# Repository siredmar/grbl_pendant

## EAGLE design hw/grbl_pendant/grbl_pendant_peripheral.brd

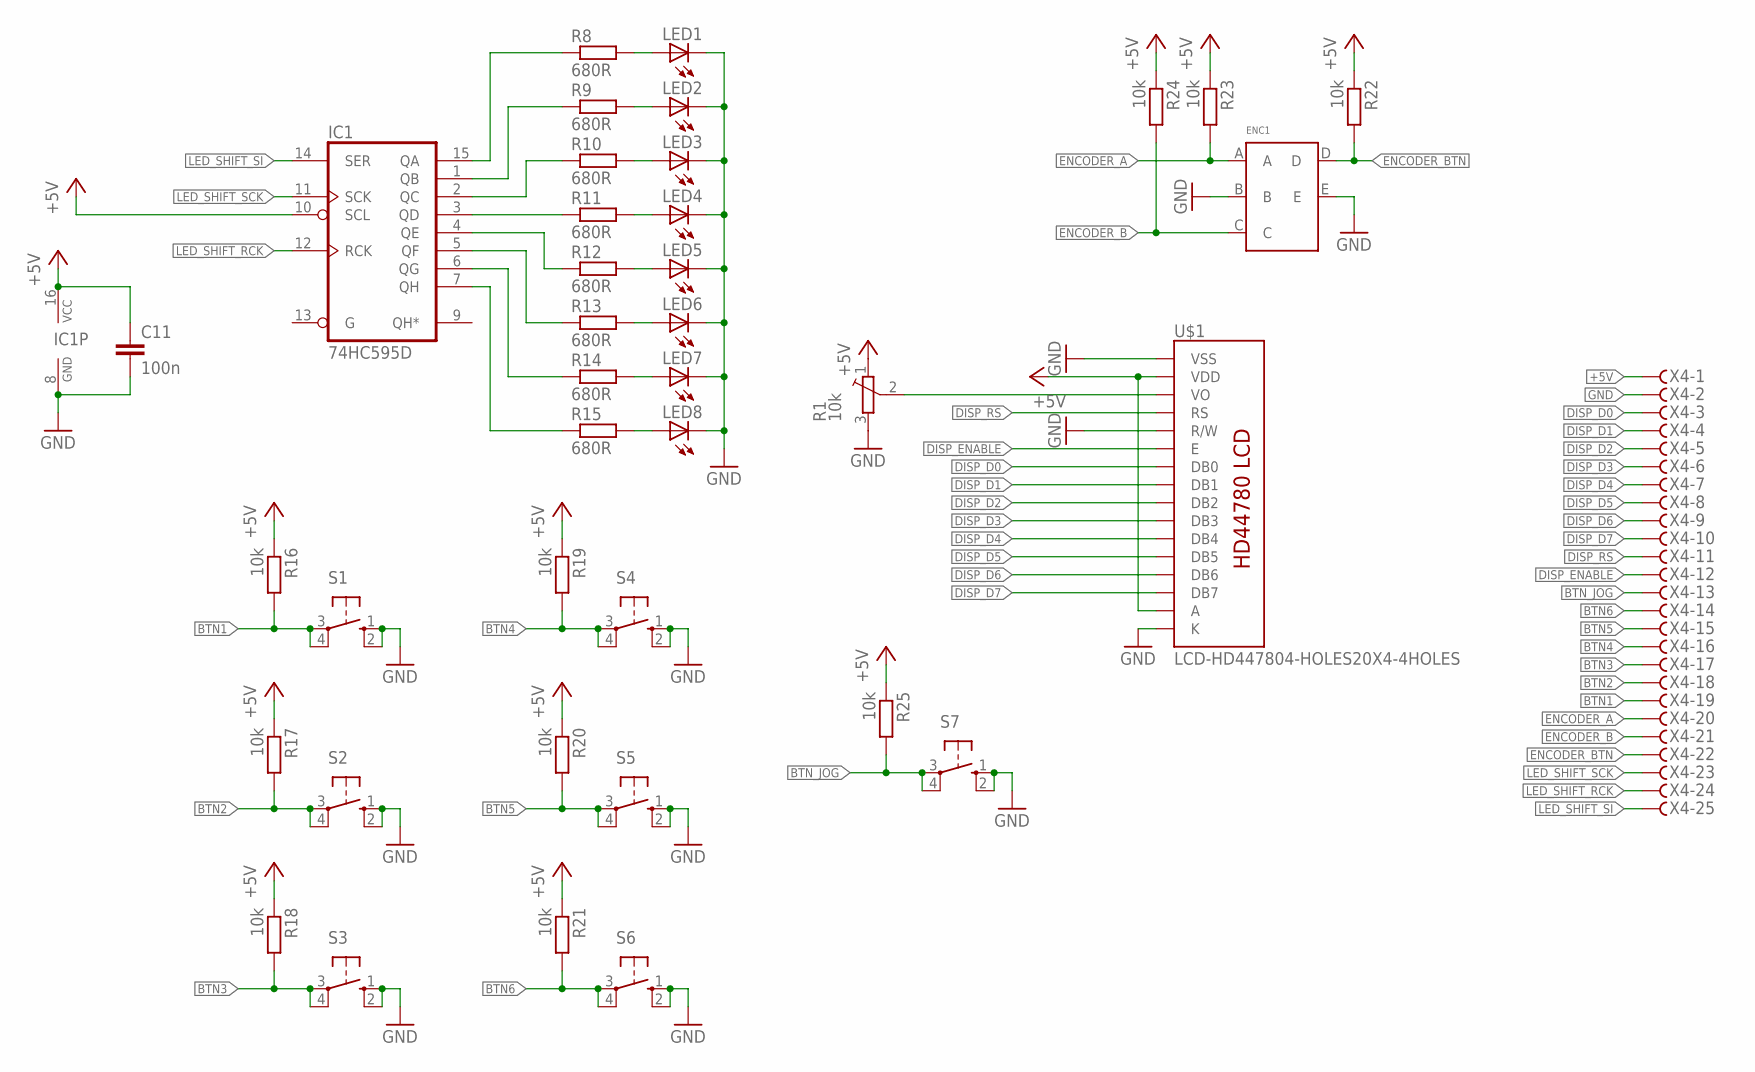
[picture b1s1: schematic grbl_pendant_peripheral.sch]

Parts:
C11: 100n; C0603K
ENC1: ENCODER
IC1: 74HC595D; SO16
LED1, LED2, LED3, LED4, LED5, LED6, LED7, LED8: LED5MM
R1: 10k; 35WR5KLFTR
R8, R9, R10, R11, R12, R13, R14, R15: 680R; R0603
R16, R17, R18, R19, R20, R21, R22, R23, R24, R25: 10k; R0603
S1, S2, S3, S4, S5, S6, S7: 10-XX; B3F-10XX
U$1: LCD-HD447804-HOLES20X4-4HOLES; LCD-20X4-4HOLES
X4: F25HPS; F25HP

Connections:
+5V: C11.1, IC1.10 (SCL), IC1.16 (VCC), R1.1 (E), R16.1, R17.1, R18.1, R19.1, R20.1, R21.1, R22.1, R23.1, R24.1, R25.1, U$1.P$2 (VDD), U$1.P$15 (A), X4.1
BTN1: R16.2, S1.3, S1.4 (P1), X4.19
BTN2: R17.2, S2.3, S2.4 (P1), X4.18
BTN3: R18.2, S3.3, S3.4 (P1), X4.17
BTN4: R19.2, S4.3, S4.4 (P1), X4.16
BTN5: R20.2, S5.3, S5.4 (P1), X4.15
BTN6: R21.2, S6.3, S6.4 (P1), X4.14
BTN_JOG: R25.2, S7.3, S7.4 (P1), X4.13
DISP_D0: U$1.P$7 (DB0), X4.3
DISP_D1: U$1.P$8 (DB1), X4.4
DISP_D2: U$1.P$9 (DB2), X4.5
DISP_D3: U$1.P$10 (DB3), X4.6
DISP_D4: U$1.P$11 (DB4), X4.7
DISP_D5: U$1.P$12 (DB5), X4.8
DISP_D6: U$1.P$13 (DB6), X4.9
DISP_D7: U$1.P$14 (DB7), X4.10
DISP_ENABLE: U$1.P$6 (E), X4.12
DISP_RS: U$1.P$4 (RS), X4.11
ENCODER_A: ENC1.A, R23.2, X4.20
ENCODER_B: ENC1.C, R24.2, X4.21
ENCODER_BTN: ENC1.D, R22.2, X4.22
GND: C11.2, ENC1.B, ENC1.E, IC1.8 (GND), LED1.K (C), LED2.K (C), LED3.K (C), LED4.K (C), LED5.K (C), LED6.K (C), LED7.K (C), LED8.K (C), R1.3 (A), S1.1 (S), S1.2 (S1), S2.1 (S), S2.2 (S1), S3.1 (S), S3.2 (S1), S4.1 (S), S4.2 (S1), S5.1 (S), S5.2 (S1), S6.1 (S), S6.2 (S1), S7.1 (S), S7.2 (S1), U$1.P$1 (VSS), U$1.P$5 (R/W), U$1.P$16 (K), X4.2
LED_SHIFT_RCK: IC1.12 (RCK), X4.24
LED_SHIFT_SCK: IC1.11 (SCK), X4.23
LED_SHIFT_SI: IC1.14 (SER), X4.25
unnamed: IC1.3 (QD), R11.1
unnamed: IC1.15 (QA), R8.1
unnamed: IC1.1 (QB), R9.1
unnamed: IC1.2 (QC), R10.1
unnamed: R1.2 (S), U$1.P$3 (VO)
unnamed: IC1.4 (QE), R12.1
unnamed: IC1.5 (QF), R13.1
unnamed: IC1.6 (QG), R14.1
unnamed: IC1.7 (QH), R15.1
unnamed: LED1.A, R8.2
unnamed: LED2.A, R9.2
unnamed: LED3.A, R10.2
unnamed: LED4.A, R11.2
unnamed: LED5.A, R12.2
unnamed: LED6.A, R13.2
unnamed: LED7.A, R14.2
unnamed: LED8.A, R15.2

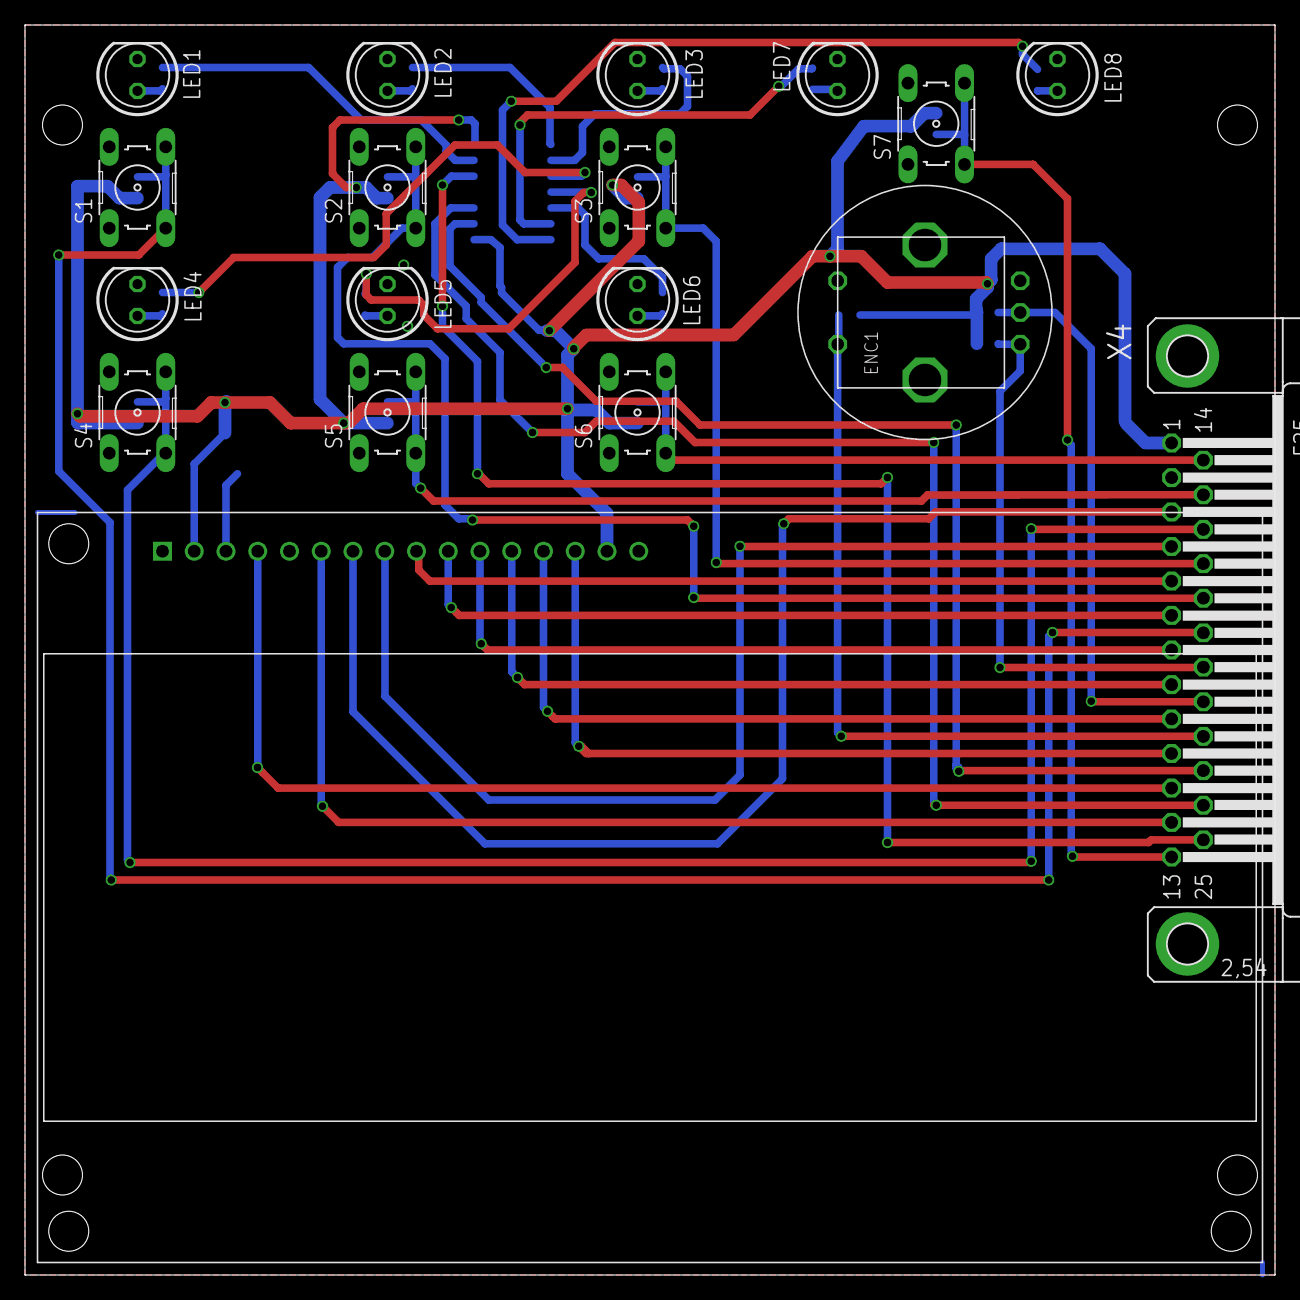
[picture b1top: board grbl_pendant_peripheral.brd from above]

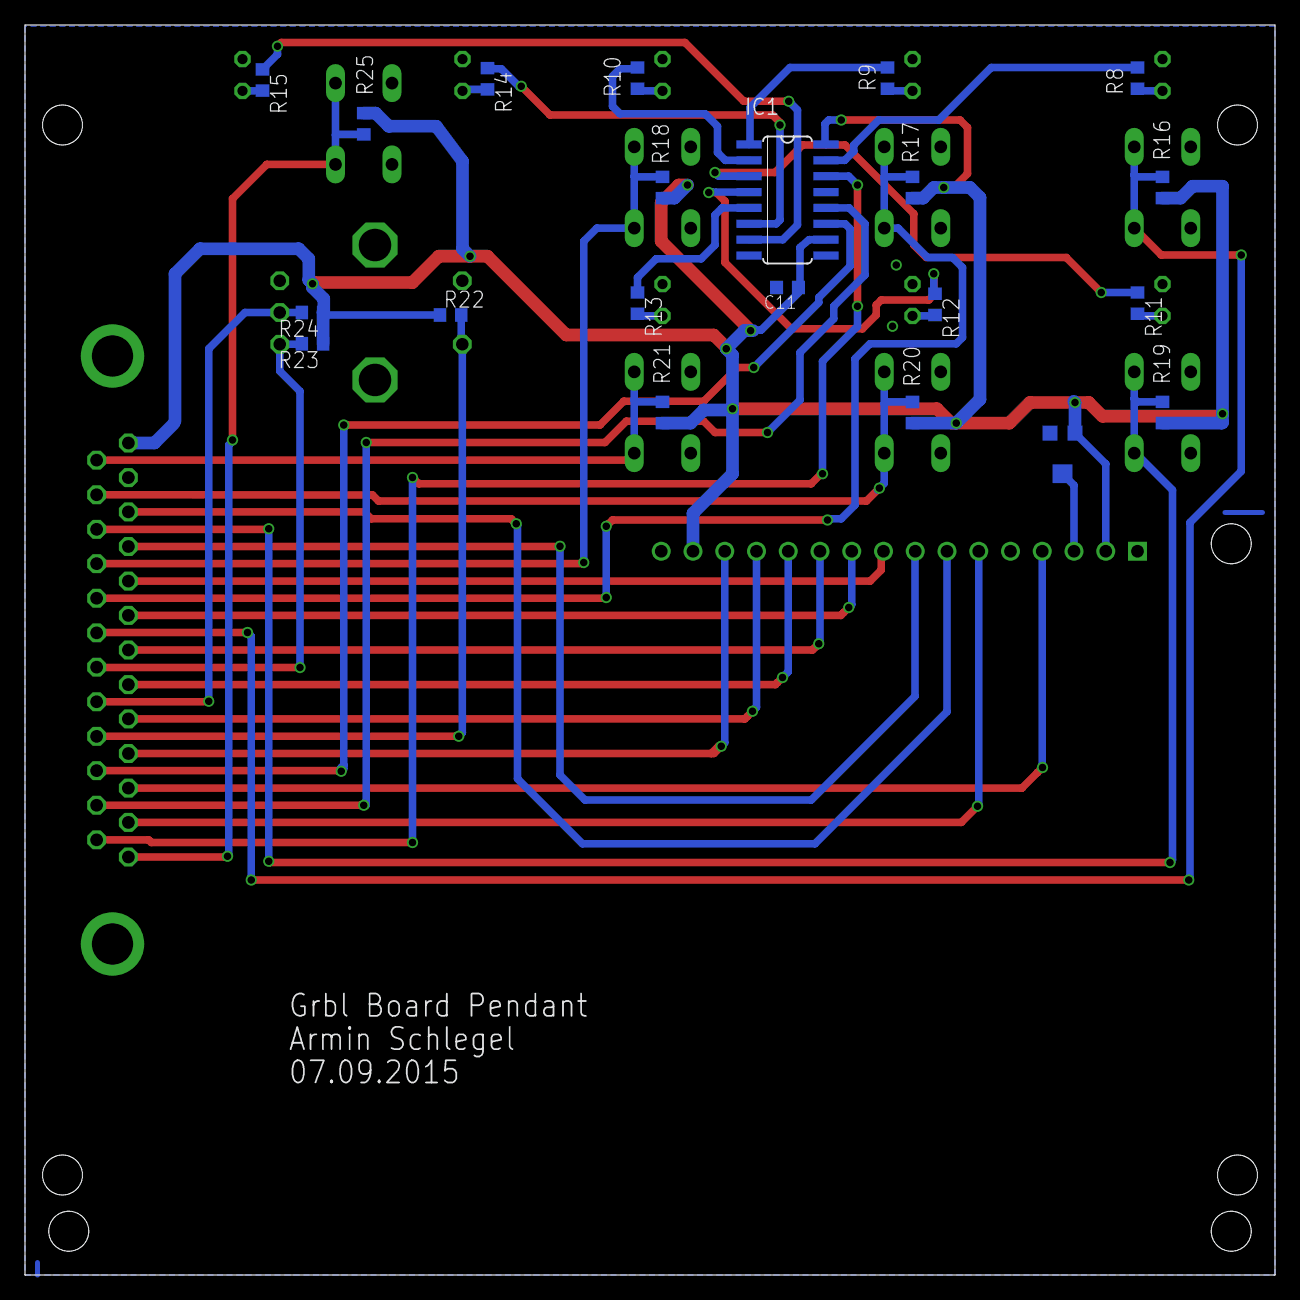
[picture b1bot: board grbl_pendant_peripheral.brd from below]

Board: 2 copper layers, 100.0 x 100.0 mm, 39 parts (21 on the bottom side), 42 nets.

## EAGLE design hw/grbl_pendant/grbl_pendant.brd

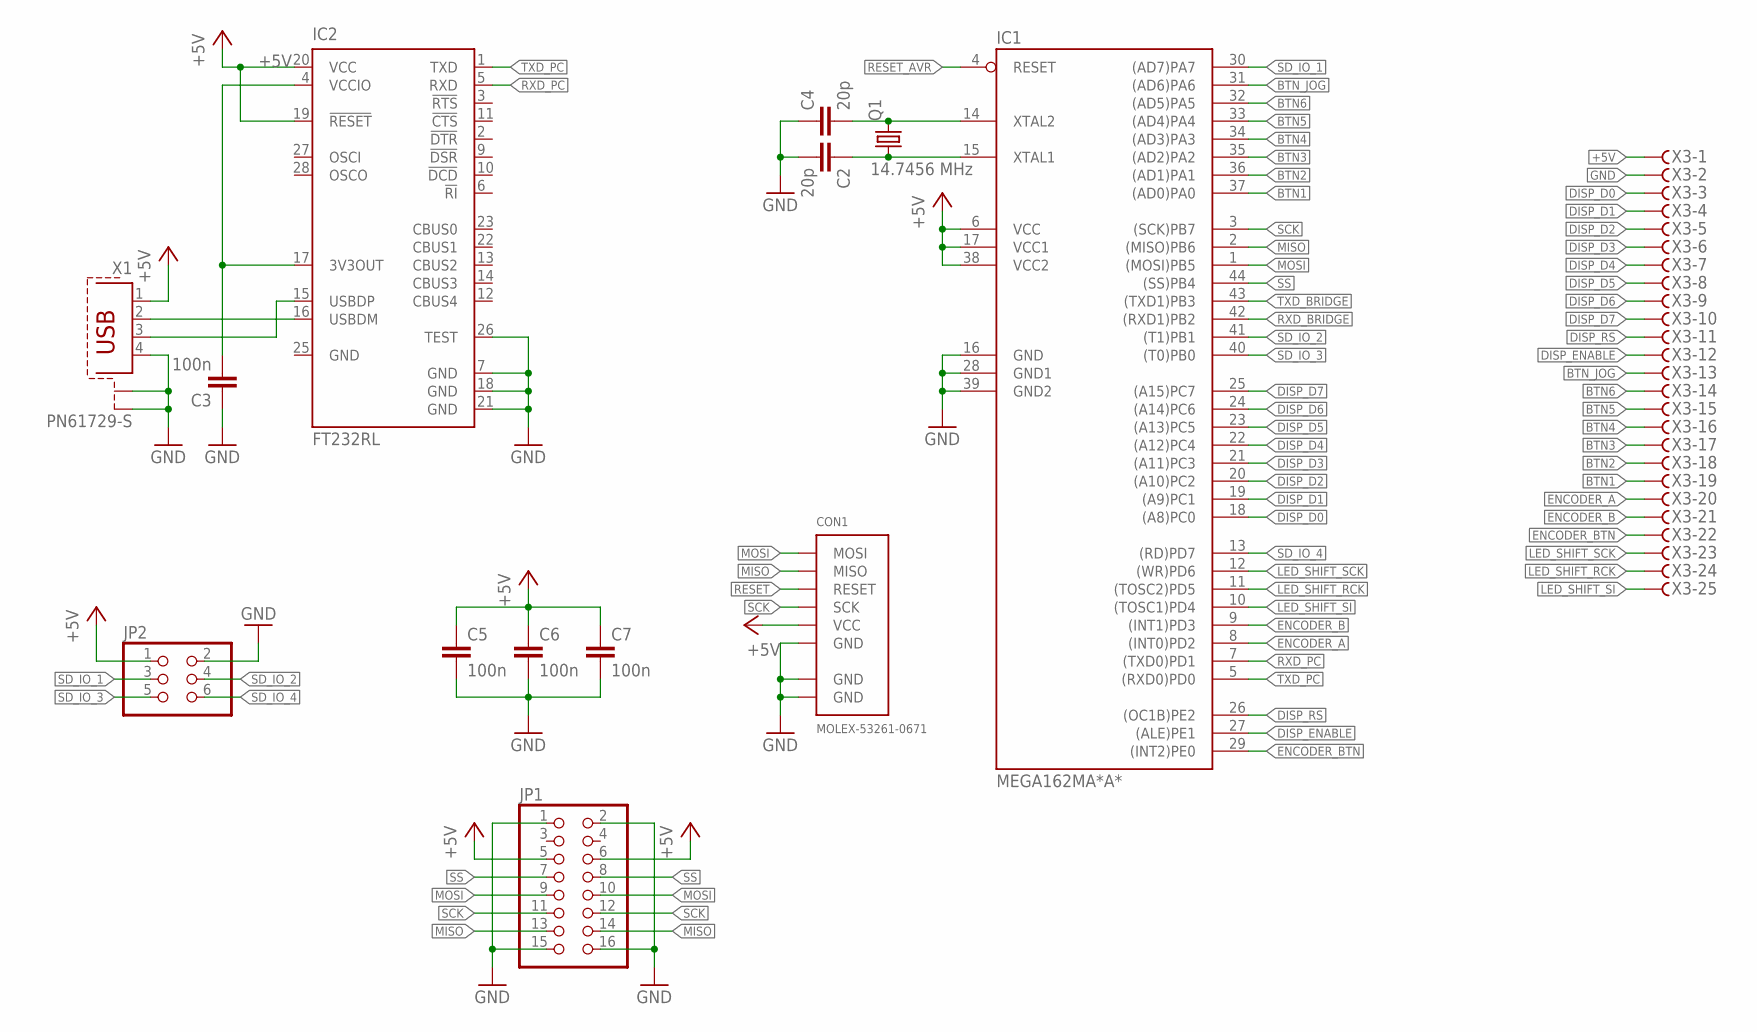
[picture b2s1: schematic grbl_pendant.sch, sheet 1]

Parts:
C2, C4: 20p; C0603K
C3: 100n; C0603
C5, C6, C7: 100n; C0603K
CON1: MOLEX-53261-0671
IC1: MEGA162MA*A*; TQFP44
IC2: FT232RL; SSOP28
JP1: PINHD-2X08_2.54; 2X08
JP2: PINHD-2X03_2.54; 2X03
Q1: 14.7456 MHz; HC49UP
X1: PN61729-S
X3: F25HPS; F25HP

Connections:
!RESET: CON1.3 (RESET)
+5V: C5.1, C6.1, C7.1, CON1.5 (VCC), IC1.6 (VCC), IC1.17 (VCC1), IC1.38 (VCC2), IC2.19 (!RESET), IC2.20 (VCC), JP1.5, JP1.6, JP2.1, X1.1, X3.1; also elsewhere on the board
BTN1: IC1.37 ((AD0)PA0), X3.19
BTN2: IC1.36 ((AD1)PA1), X3.18
BTN3: IC1.35 ((AD2)PA2), X3.17
BTN4: IC1.34 ((AD3)PA3), X3.16
BTN5: IC1.33 ((AD4)PA4), X3.15
BTN6: IC1.32 ((AD5)PA5), X3.14
BTN_JOG: IC1.31 ((AD6)PA6), X3.13
DISP_D0: IC1.18 ((A8)PC0), X3.3
DISP_D1: IC1.19 ((A9)PC1), X3.4
DISP_D2: IC1.20 ((A10)PC2), X3.5
DISP_D3: IC1.21 ((A11)PC3), X3.6
DISP_D4: IC1.22 ((A12)PC4), X3.7
DISP_D5: IC1.23 ((A13)PC5), X3.8
DISP_D6: IC1.24 ((A14)PC6), X3.9
DISP_D7: IC1.25 ((A15)PC7), X3.10
DISP_ENABLE: IC1.27 ((ALE)PE1), X3.12
DISP_RS: IC1.26 ((OC1B)PE2), X3.11
ENCODER_A: IC1.8 ((INT0)PD2), X3.20
ENCODER_B: IC1.9 ((INT1)PD3), X3.21
ENCODER_BTN: IC1.29 ((INT2)PE0), X3.22
GND: C2.2, C3.1, C4.1, C5.2, C6.2, C7.2, CON1.6 (GND), CON1.GND@1 (GND), CON1.GND@2 (GND), IC1.16 (GND), IC1.28 (GND1), IC1.39 (GND2), IC2.7 (GND), IC2.18 (GND), IC2.21 (GND), IC2.25 (GND), IC2.26 (TEST), JP1.1, JP1.2, JP1.15, JP1.16, JP2.2, X1.4, X1.S1, X1.S2, X3.2; also elsewhere on the board
LED_SHIFT_RCK: IC1.11 ((TOSC2)PD5), X3.24
LED_SHIFT_SCK: IC1.12 ((WR)PD6), X3.23
LED_SHIFT_SI: IC1.10 ((TOSC1)PD4), X3.25
MISO: CON1.2 (MISO), IC1.2 ((MISO)PB6), JP1.13, JP1.14
MOSI: CON1.1 (MOSI), IC1.1 ((MOSI)PB5), JP1.9, JP1.10
unnamed: C3.2, IC2.4 (VCCIO), IC2.17 (3V3OUT)
unnamed: C4.2, IC1.14 (XTAL2), Q1.2
unnamed: C2.1, IC1.15 (XTAL1), Q1.1
RESET_AVR: IC1.4 (RESET); also elsewhere on the board
RXD_BRIDGE: IC1.42 ((RXD1)PB2); also elsewhere on the board
RXD_PC: IC1.7 ((TXD0)PD1), IC2.5 (RXD)
SCK: CON1.4 (SCK), IC1.3 ((SCK)PB7), JP1.11, JP1.12
SD_IO_1: IC1.30 ((AD7)PA7), JP2.3
SD_IO_2: IC1.41 ((T1)PB1), JP2.4
SD_IO_3: IC1.40 ((T0)PB0), JP2.5
SD_IO_4: IC1.13 ((RD)PD7), JP2.6
SS: IC1.44 ((SS)PB4), JP1.7, JP1.8
TXD_BRIDGE: IC1.43 ((TXD1)PB3); also elsewhere on the board
TXD_PC: IC1.5 ((RXD0)PD0), IC2.1 (TXD)
USBDM: IC2.16 (USBDM), X1.2
USBDP: IC2.15 (USBDP), X1.3

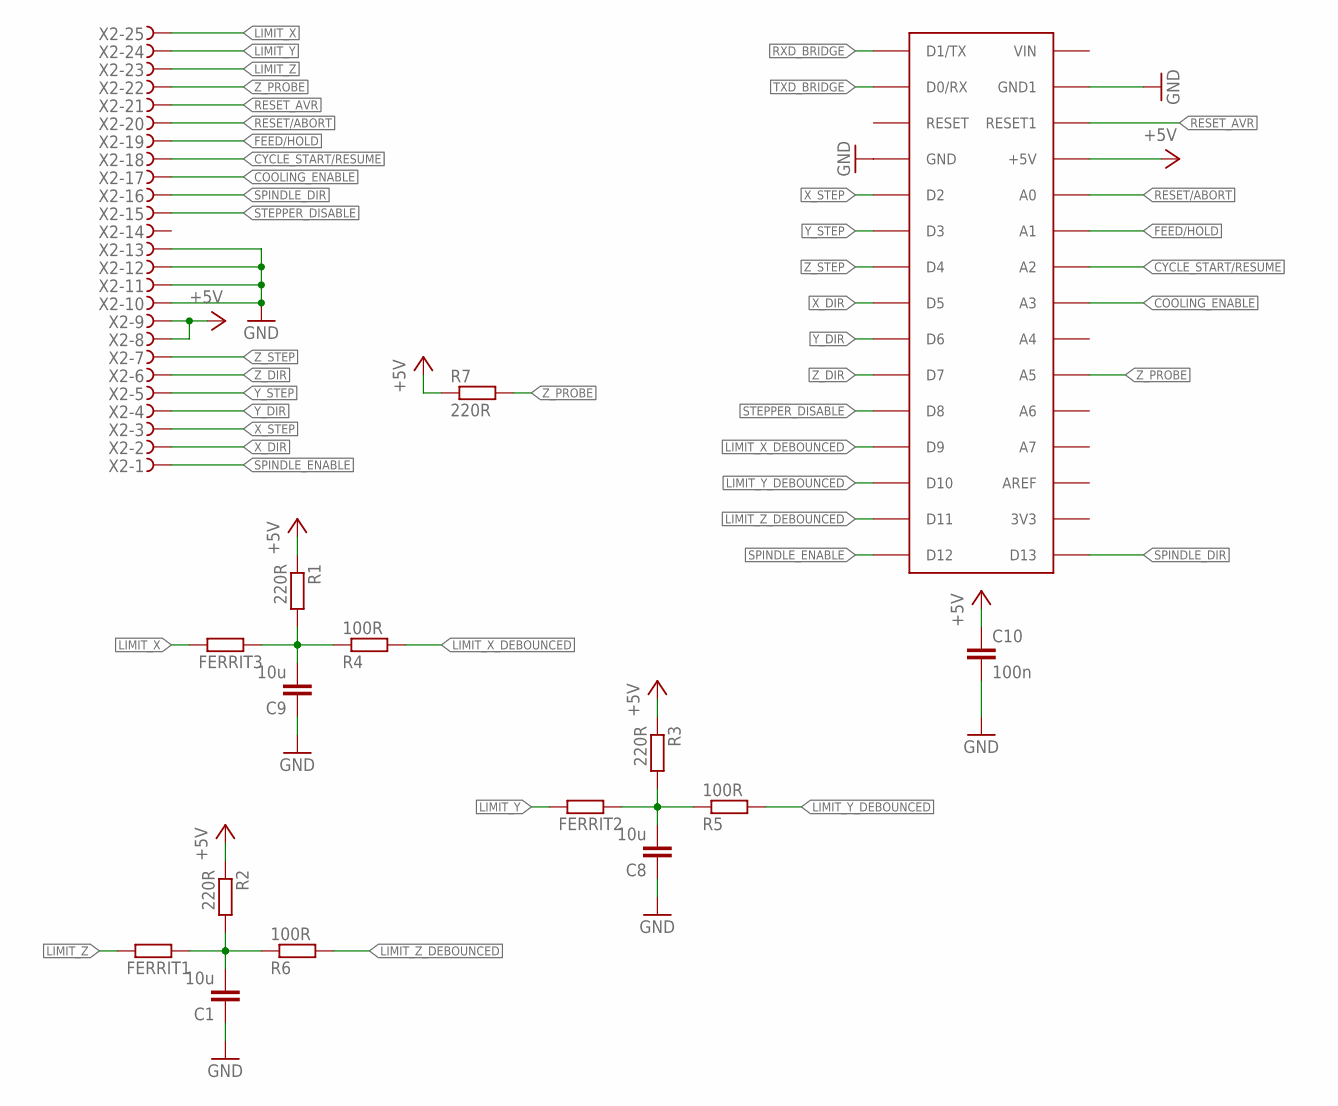
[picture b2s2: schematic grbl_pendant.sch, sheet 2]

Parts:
C1, C8, C9: 10u; C0805
C10: 100n; C0805
FERRIT1, FERRIT2, FERRIT3: R-EU_M0805; M0805
R1, R2, R3, R7: 220R; R0603
R4, R5, R6: 100R; R0603
U$2: ARDUINONANO; PDIP-32
X2: F25HPS; F25HP

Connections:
+5V: C10.1, R1.1, R2.1, R3.1, R7.1, U$2.+5V, X2.8, X2.9; also elsewhere on the board
COOLING_ENABLE: U$2.A3, X2.17
CYCLE_START/RESUME: U$2.A2, X2.18
FEED/HOLD: U$2.A1, X2.19
GND: C1.1, C8.1, C9.1, C10.2, U$2.GND, U$2.GND1, X2.10, X2.11, X2.12, X2.13; also elsewhere on the board
LIMIT_INT_X: C9.2, FERRIT3.2, R1.2, R4.1
LIMIT_INT_Y: C8.2, FERRIT2.2, R3.2, R5.1
LIMIT_INT_Z: C1.2, FERRIT1.2, R2.2, R6.1
LIMIT_X: FERRIT3.1, X2.25
LIMIT_X_DEBOUNCED: R4.2, U$2.D9
LIMIT_Y: FERRIT2.1, X2.24
LIMIT_Y_DEBOUNCED: R5.2, U$2.D10
LIMIT_Z: FERRIT1.1, X2.23
LIMIT_Z_DEBOUNCED: R6.2, U$2.D11
RESET/ABORT: U$2.A0, X2.20
RESET_AVR: U$2.RESET1, X2.21; also elsewhere on the board
RXD_BRIDGE: U$2.D1/TX; also elsewhere on the board
SPINDLE_DIR: U$2.D13, X2.16
SPINDLE_ENABLE: U$2.D12, X2.1
STEPPER_DISABLE: U$2.D8, X2.15
TXD_BRIDGE: U$2.D0/RX; also elsewhere on the board
X_DIR: U$2.D5, X2.2
X_STEP: U$2.D2, X2.3
Y_DIR: U$2.D6, X2.4
Y_STEP: U$2.D3, X2.5
Z_DIR: U$2.D7, X2.6
Z_PROBE: R7.2, U$2.A5, X2.22
Z_STEP: U$2.D4, X2.7

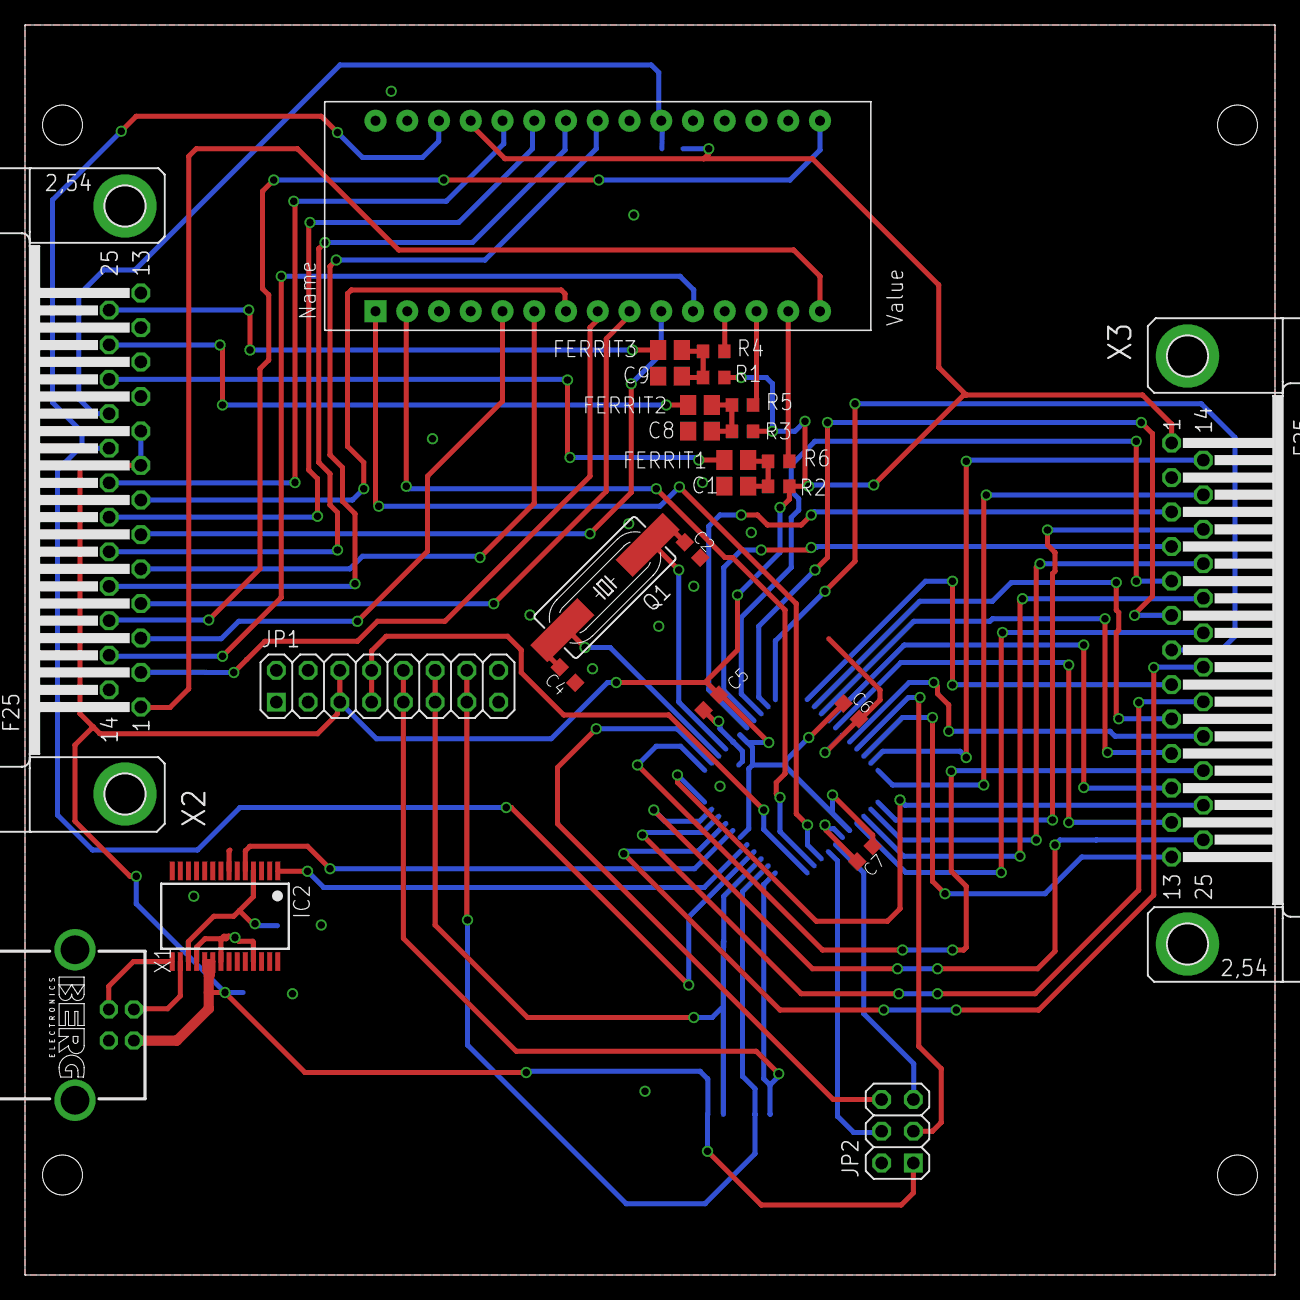
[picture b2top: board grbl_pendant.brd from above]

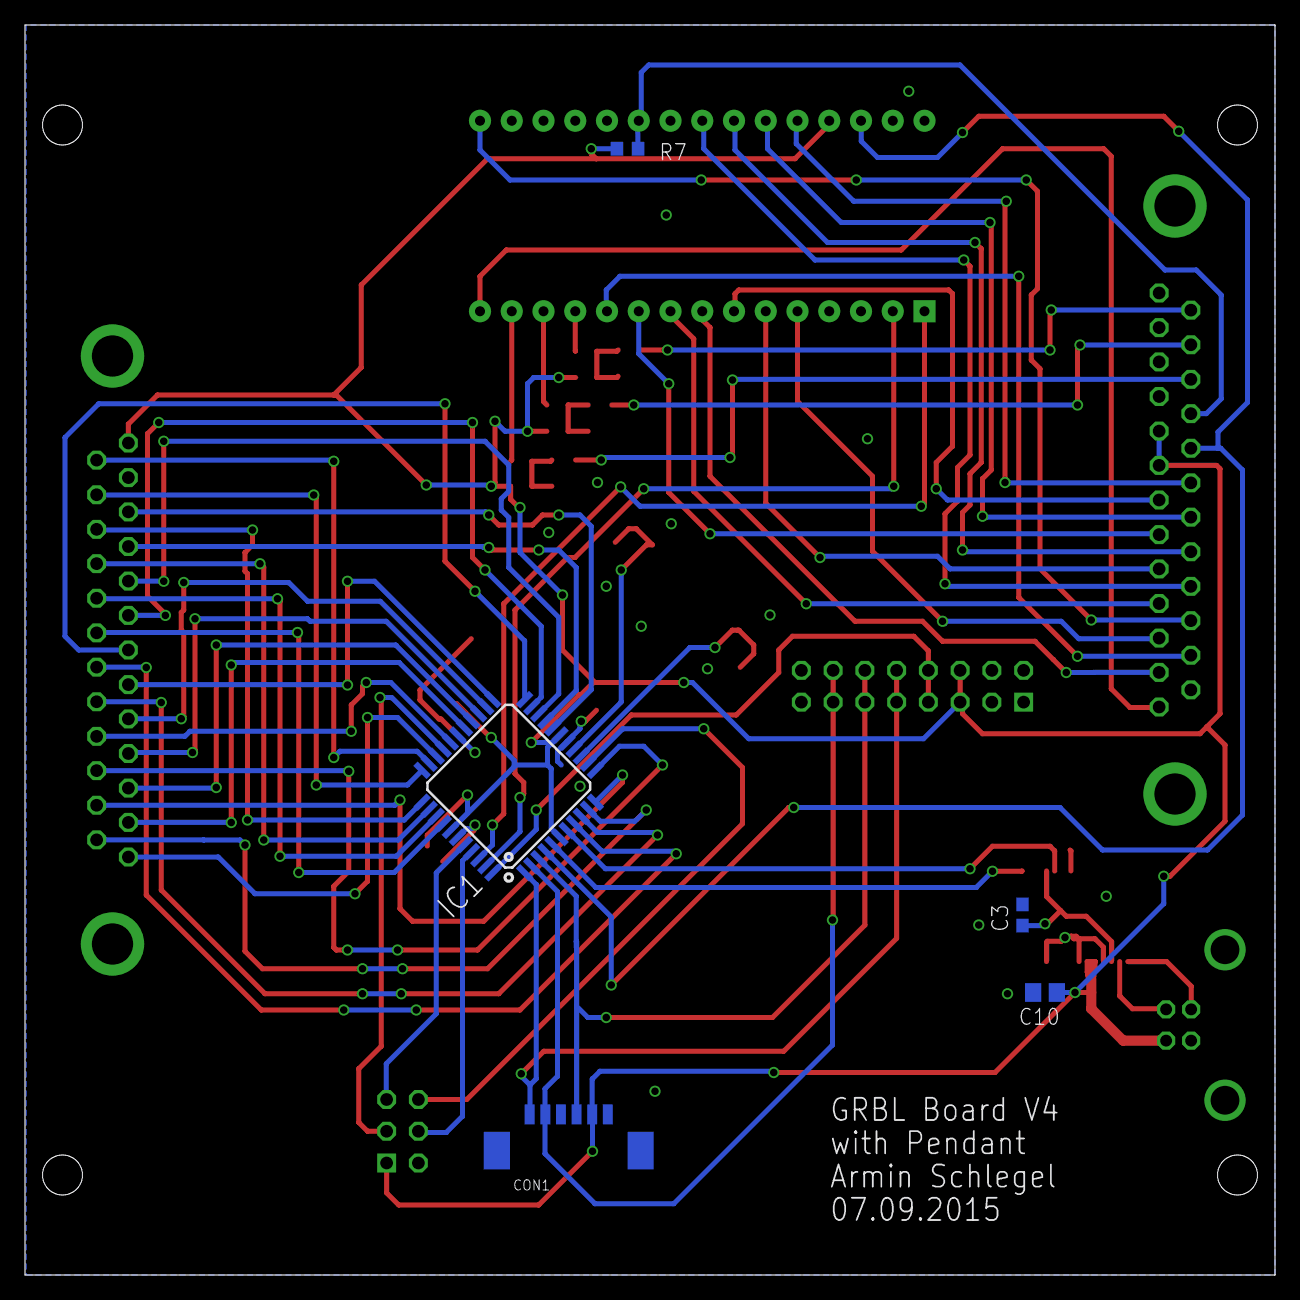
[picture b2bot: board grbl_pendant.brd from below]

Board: 2 copper layers, 100.0 x 100.0 mm, 30 parts (5 on the bottom side), 66 nets.

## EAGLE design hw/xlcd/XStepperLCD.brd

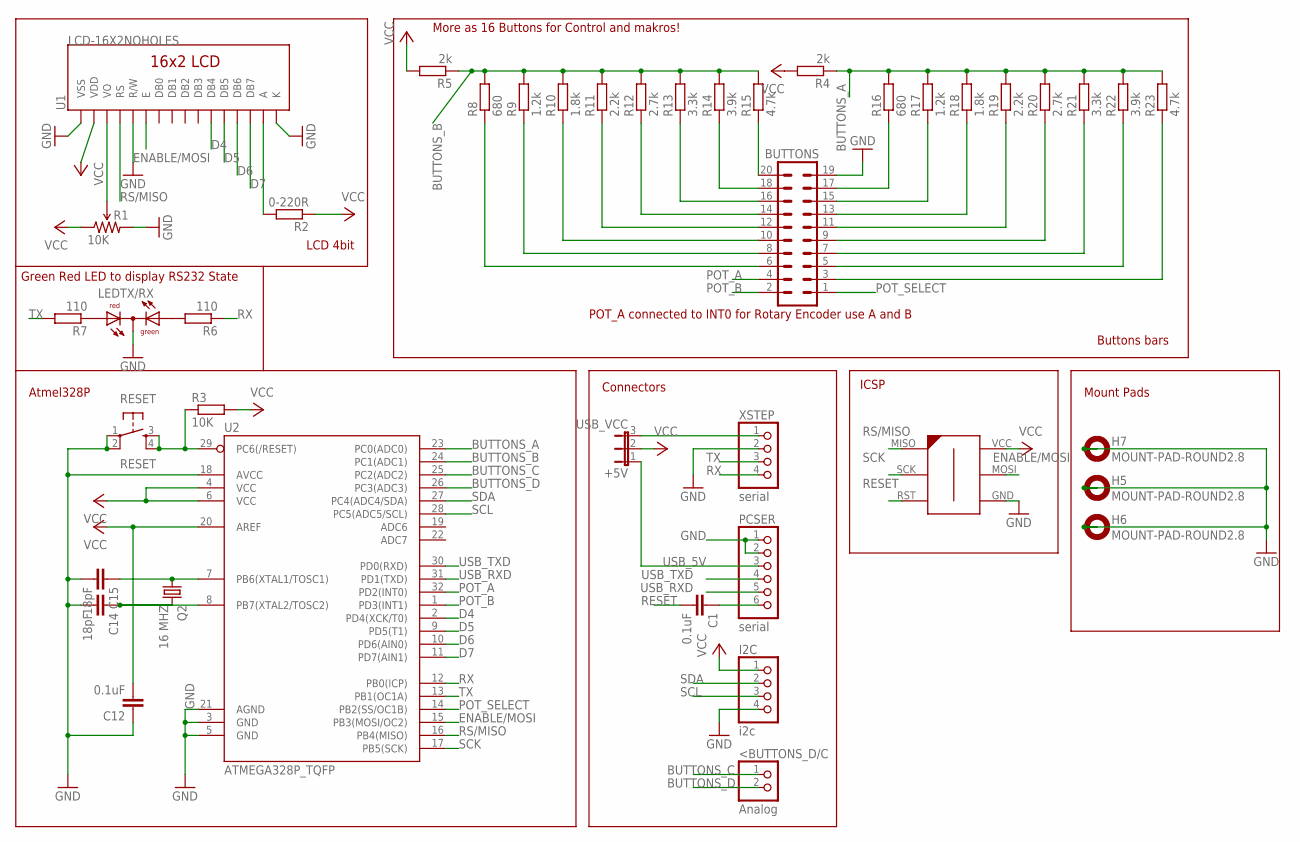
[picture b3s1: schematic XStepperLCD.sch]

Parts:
+5V: USB_VCC; JP2
<BUTTONS_D/C: Analog; 1X02
BUTTONS: ML20
C1, C12: 0.1uF; C1206
C14, C15: 18pF; C1206
H5, H6, H7: MOUNT-PAD-ROUND2.8; 2,8-PAD
I2C: i2c; 1X04/90
ICSP: ICSP; 6PAD_ISP
LEDTX/RX: DUOLED2X5
PCSER: serial; 1X06/90
Q2: 16 MHZ; HC49/S
R1: 10K; 3362U-2
R2: 0-220R; R1206
R3: 10K; R1206
R4, R5: 2k; R1206
R6, R7: 110; R1206
R8, R16: 680; R1206
R9, R17: 1.2k; R1206
R10, R18: 1.8k; R1206
R11, R19: 2.2k; R1206
R12, R20: 2.7k; R1206
R13, R21: 3.3k; R1206
R14, R22: 3.9k; R1206
R15, R23: 4.7k; R1206
RESET: RESET; TACTILE_SWITCH_SMD
U1: LCD-16X2NOHOLES; LCD-16X2_NOHOLES
U2: ATMEGA328P_TQFP; TQFP32-08
XSTEP: serial; 1X04/90

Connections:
BUTTONS_A: R4.1, R16.2, R17.2, R18.2, R19.2, R20.2, R21.2, R22.2, R23.2, U2.23 (PC0(ADC0))
BUTTONS_B: R5.1, R8.2, R9.2, R10.2, R11.2, R12.2, R13.2, R14.2, R15.2, U2.24 (PC1(ADC1))
BUTTONS_C: <BUTTONS_D/C.1, U2.25 (PC2(ADC2))
BUTTONS_D: <BUTTONS_D/C.2, U2.26 (PC3(ADC3))
D4: U1.11 (DB4), U2.2 (PD4(XCK/T0))
D5: U1.12 (DB5), U2.9 (PD5(T1))
D6: U1.13 (DB6), U2.10 (PD6(AIN0))
D7: U1.14 (DB7), U2.11 (PD7(AIN1))
ENABLE/MOSI: ICSP.MOSI, U1.6 (E), U2.15 (PB3(MOSI/OC2))
GND: BUTTONS.19, C12.1, C14.2, C15.2, H5.B2,8, H6.B2,8, H7.B2,8, I2C.4, ICSP.GND, LEDTX/RX.K (C), PCSER.1, PCSER.2, R1.3 (CW), RESET.1, RESET.2, U1.1 (VSS), U1.5 (R/W), U1.16 (K), U2.3 (GND), U2.5 (GND), U2.18 (AVCC), U2.21 (AGND), XSTEP.2
unnamed: R1.2 (WIPER), U1.3 (VO)
unnamed: R2.2, U1.15 (A)
unnamed: BUTTONS.13, R18.1
unnamed: BUTTONS.15, R17.1
unnamed: BUTTONS.17, R16.1
unnamed: BUTTONS.6, R8.1
unnamed: BUTTONS.8, R9.1
unnamed: BUTTONS.3, R23.1
unnamed: BUTTONS.5, R22.1
unnamed: BUTTONS.10, R10.1
unnamed: BUTTONS.12, R11.1
unnamed: BUTTONS.14, R12.1
unnamed: C1.1, PCSER.6
unnamed: BUTTONS.16, R13.1
unnamed: BUTTONS.7, R21.1
unnamed: BUTTONS.9, R20.1
unnamed: BUTTONS.11, R19.1
unnamed: BUTTONS.18, R14.1
unnamed: BUTTONS.20, R15.1
unnamed: LEDTX/RX.AG, R6.2
unnamed: LEDTX/RX.AR, R7.1
unnamed: C15.1, Q2.1, U2.7 (PB6(XTAL1/TOSC1))
unnamed: C14.1, Q2.2, U2.8 (PB7(XTAL2/TOSC2))
POT_A: BUTTONS.4, U2.32 (PD2(INT0))
POT_B: BUTTONS.2, U2.1 (PD3(INT1))
POT_SELECT: BUTTONS.1, U2.14 (PB2(SS/OC1B))
RESET: C1.2, ICSP.RST, R3.1, RESET.3, RESET.4, U2.29 (PC6(/RESET))
RS/MISO: ICSP.MISO, U1.4 (RS), U2.16 (PB4(MISO))
RX: R6.1, U2.12 (PB0(ICP)), XSTEP.4
SCK: ICSP.SCK, U2.17 (PB5(SCK))
SCL: I2C.3, U2.28 (PC5(ADC5/SCL))
SDA: I2C.2, U2.27 (PC4(ADC4/SDA))
TX: R7.2, U2.13 (PB1(OC1A)), XSTEP.3
USB_5V: +5V.1, PCSER.3
USB_RXD: PCSER.5, U2.31 (PD1(TXD))
USB_TXD: PCSER.4, U2.30 (PD0(RXD))
VCC: +5V.2, C12.2, I2C.1, ICSP.VCC, R1.1 (CCW), R2.1, R3.2, R4.2, R5.2, U1.2 (VDD), U2.4 (VCC), U2.6 (VCC)
XSTEP_5V: +5V.3, XSTEP.1

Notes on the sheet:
Connectors
ICSP
Atmel328P
Mount Pads
Buttons bars
Green Red LED to display RS232 State
LCD 4bit
POT_A connected to INT0 for Rotary Encoder use A and B
More as 16 Buttons for Control and makros!

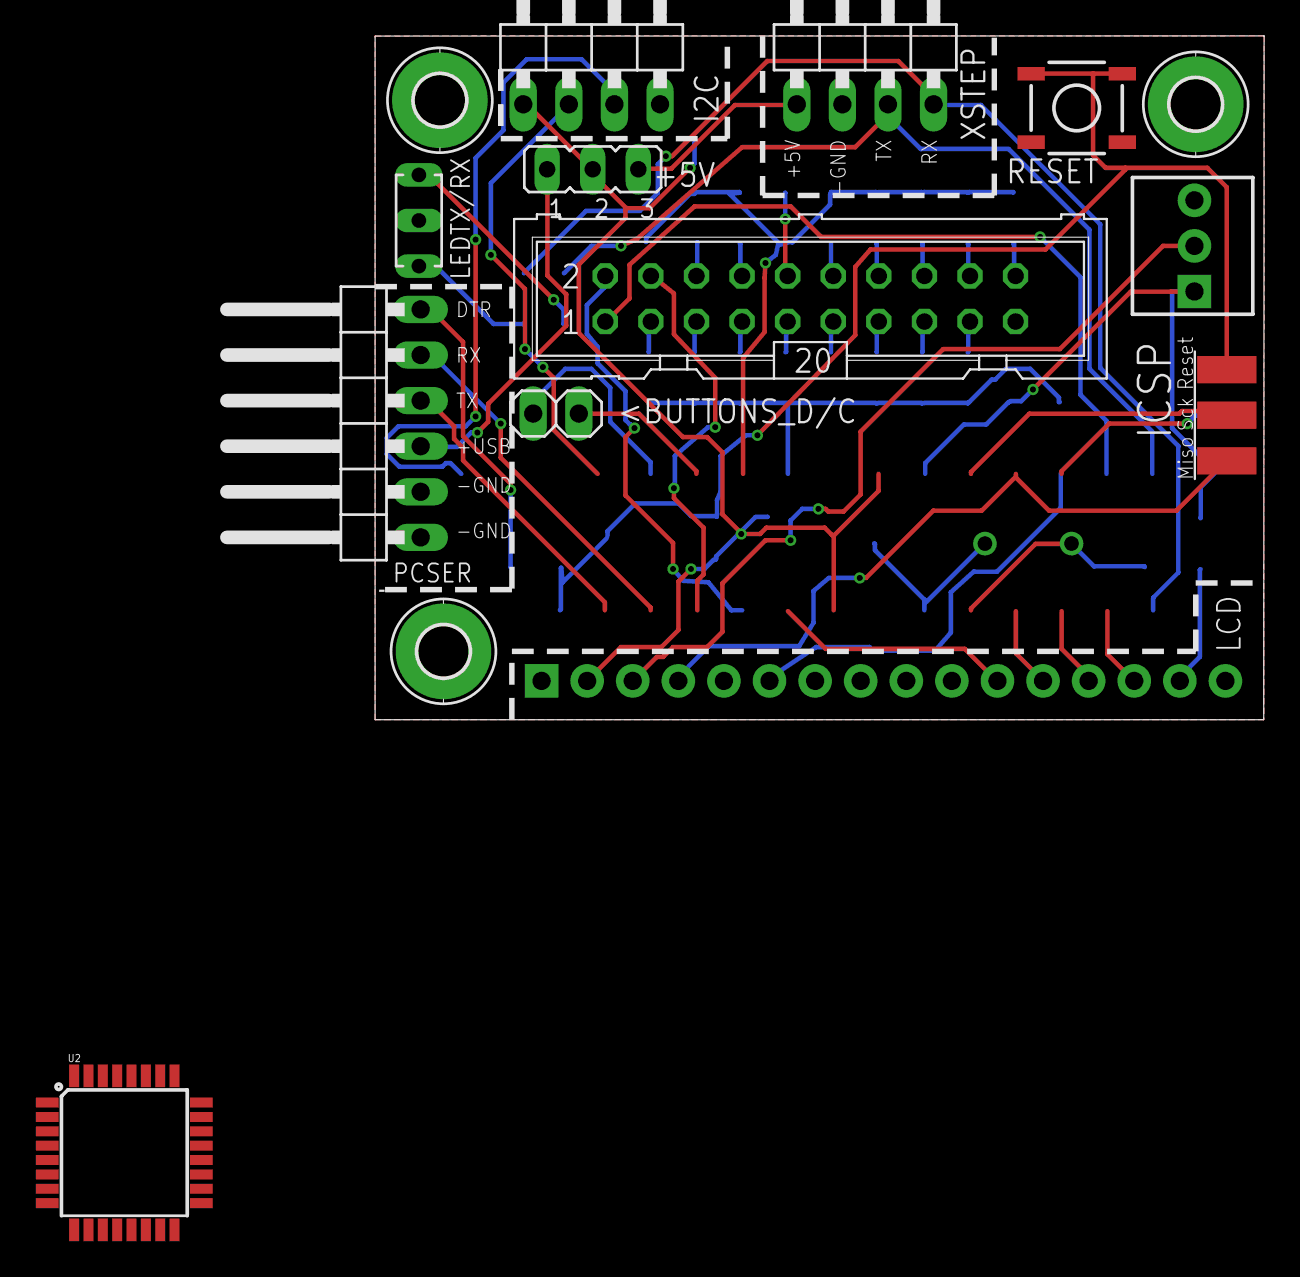
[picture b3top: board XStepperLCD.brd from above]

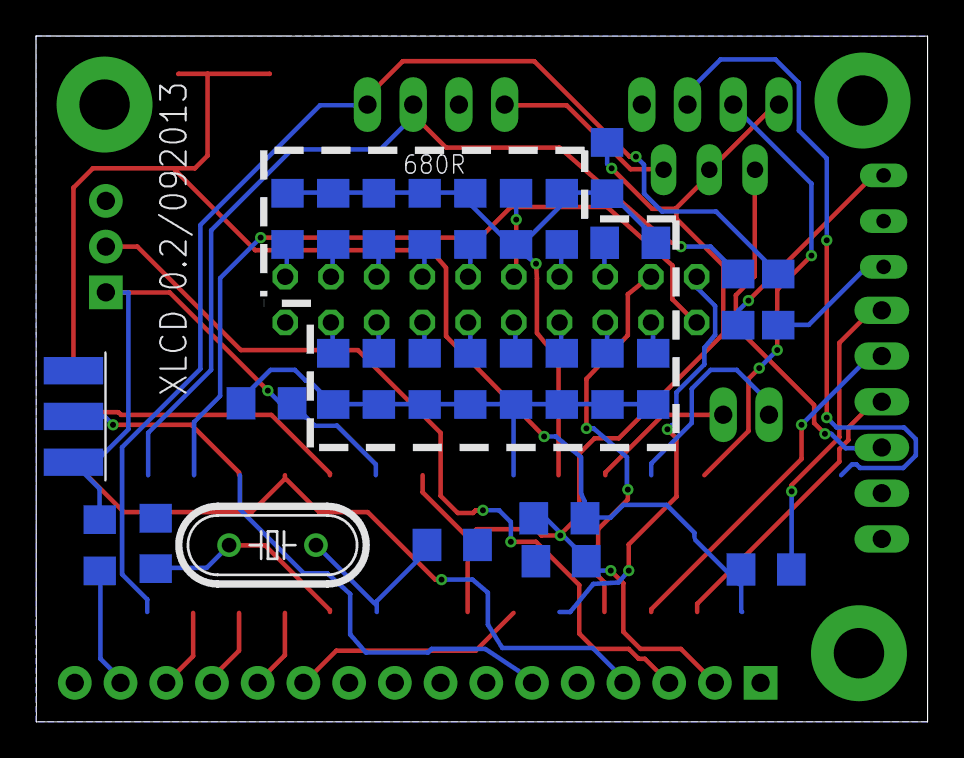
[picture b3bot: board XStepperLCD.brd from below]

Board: 2 copper layers, 49.5 x 38.1 mm, 42 parts (27 on the bottom side), 48 nets.

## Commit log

2015-07-18 first SW version with arduino nano v3
2015-08-06 sw update4
2015-08-27 sch/brd files updated
2015-09-03 grbl_pendant_peripheral v1 layout
2015-09-07 main board and pendant finished layouts
2015-09-07 removed backup files
2015-09-07 modified .gitignore for eagle backup files

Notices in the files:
parts and their libraries:
SparkFun-Electromechanical: Licensing: CC v3.0 Share-Alike You are welcome to use this library for commercial purposes.
SparkFun-DigitalIC: Licensing: Creative Commons ShareAlike 4.0 International - https://creativecommons.org/licenses/by-sa/4.0
